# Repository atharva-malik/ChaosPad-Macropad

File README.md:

# ChaosPad-Macropad
---

## Overview
ChaosPad is a macropad designed specifically for me, with every switch being. It features a 3x3 grid of buttons, an OLED display, and a rotary encoder. The macropad is also designed to be easily customizable and programmable, allowing users to create their own macros and shortcuts. It has all of the main components of a macropad, including 9 programmable switches, a rotary encoder, and an OLED display. The layout is designed to be compact and efficient, with all of the components easily accessible.

## BOM
You can check out the full BOM [here](BOM.csv). Note that all prices are in AUD unless specified otherwise.

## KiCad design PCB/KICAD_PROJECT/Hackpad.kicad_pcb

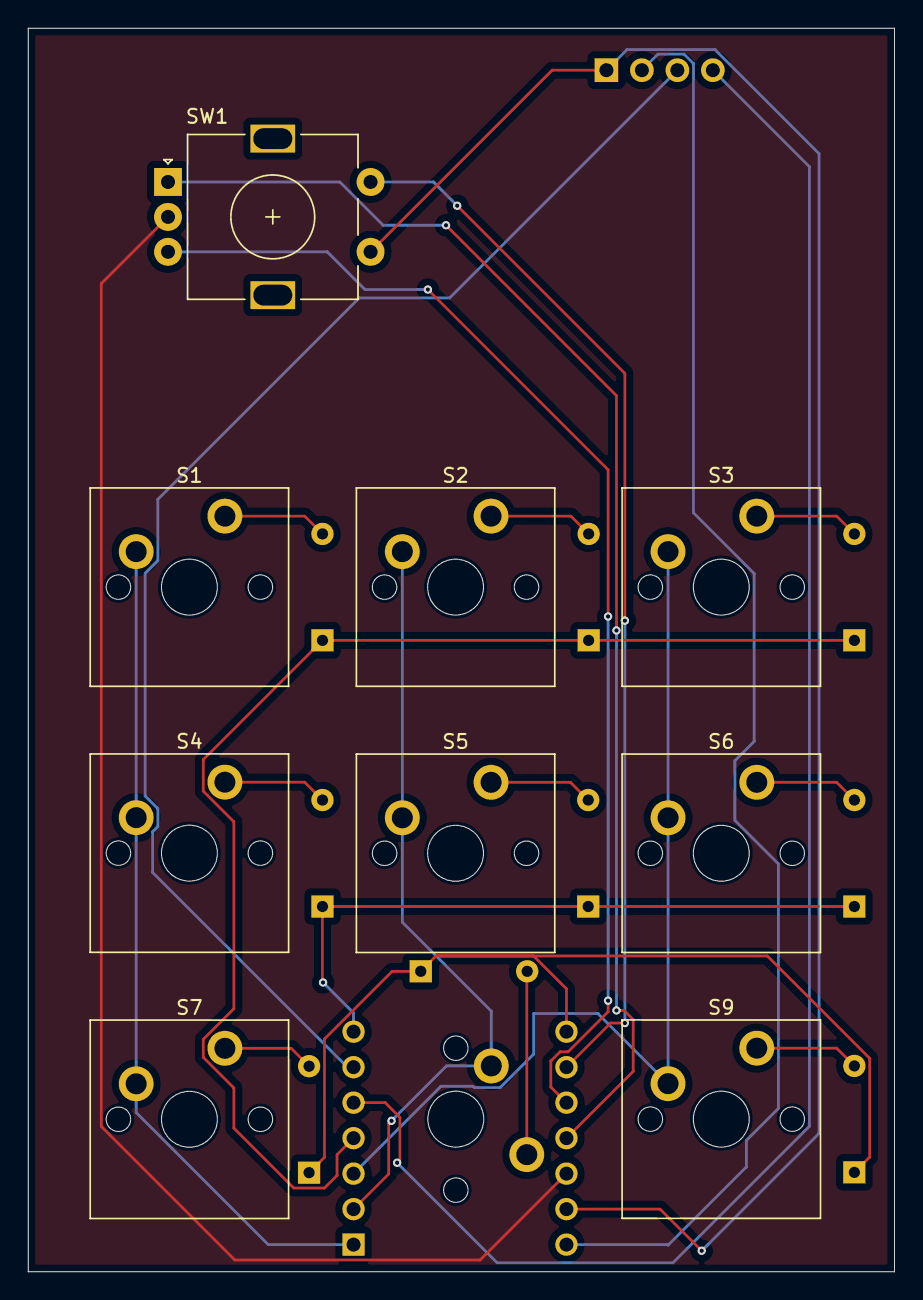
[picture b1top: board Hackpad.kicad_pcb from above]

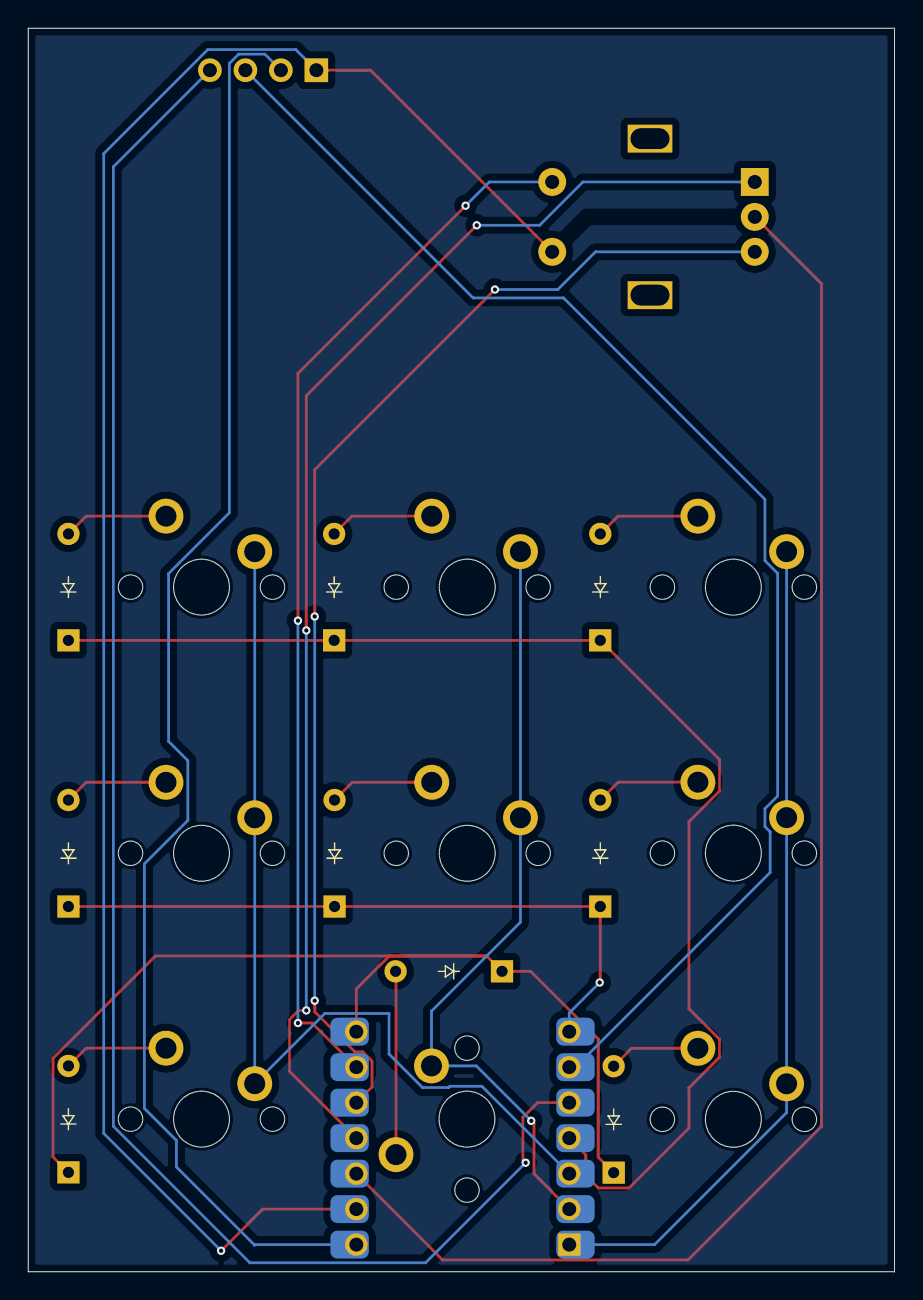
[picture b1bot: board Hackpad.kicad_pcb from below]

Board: 2 copper layers, 62.0 x 89.0 mm, 21 parts (10 on the bottom side), 23 nets.

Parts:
D1, D2, D3, D4, D5, D6, D7, D8, D9: Diode; Diode_DO-35
J1: OLED_128x64
S1, S2, S3, S4, S5, S6, S7, S8, S9: Keyswitch; MX_PCB_1.00u
SW1: RotaryEncoder_Switch; RotaryEncoder_Alps_EC11E-Switch_Vertical_H20mm
U1: MCU_Seeed_XIAO_RP2040; Seeed_XIAO_RP2040

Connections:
3.3V: SW1.C, U1.12 (3V3)
5V: J1.2 (VCC), U1.14 (5V)
COLUMN 0: S1.1, S4.1, S7.1, U1.1 (PA02_A0_D0)
COLUMN 1: S2.1, S5.1, S8.1, U1.2 (PA4_A1_D1)
COLUMN 2: S3.1, S6.1, S9.1, U1.3 (PA10_A2_D2)
GROUND: J1.1 (GND), SW1.S1, U1.13 (GND)
unnamed: D1.2 (A), S1.2
unnamed: D2.2 (A), S2.2
unnamed: D3.2 (A), S3.2
unnamed: D4.2 (A), S4.2
unnamed: D5.2 (A), S5.2
unnamed: D6.2 (A), S6.2
unnamed: D7.2 (A), S7.2
unnamed: D8.2 (A), S8.2
unnamed: D9.2 (A), S9.2
ROW 0: D1.1 (K), D2.1 (K), D3.1 (K), U1.4 (PA11_A3_D3)
ROW 1: D4.1 (K), D5.1 (K), D6.1 (K), U1.7 (PB08_A6_D6_TX)
ROW 2: D7.1 (K), D8.1 (K), D9.1 (K), U1.8 (PB09_A7_D7_RX)
RTRY A: SW1.A, U1.11 (PA6_A10_D10_MOSI)
RTRY B: SW1.B, U1.10 (PA5_A9_D9_MISO)
RTRY SWITCH: SW1.S2, U1.9 (PA7_A8_D8_SCK)
SCL: J1.3 (SCL), U1.6 (PA9_A5_D5_SCL)
SDA: J1.4 (SDA), U1.5 (PA8_A4_D4_SDA)

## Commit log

2025-05-26 Added image
2025-05-26 Added Firmware
2025-05-26 Added most of the case files
2025-05-26 added the rest of the 3d files and the pcb files
2025-05-27 Fixed routing flaw
2025-05-28 sync
2025-06-04 Added BOM
